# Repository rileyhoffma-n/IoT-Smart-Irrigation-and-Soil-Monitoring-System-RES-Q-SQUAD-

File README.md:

# IoT-Smart-Irrigation-and-Soil-Monitoring-System-RES-Q-SQUAD-
ESE senior design project

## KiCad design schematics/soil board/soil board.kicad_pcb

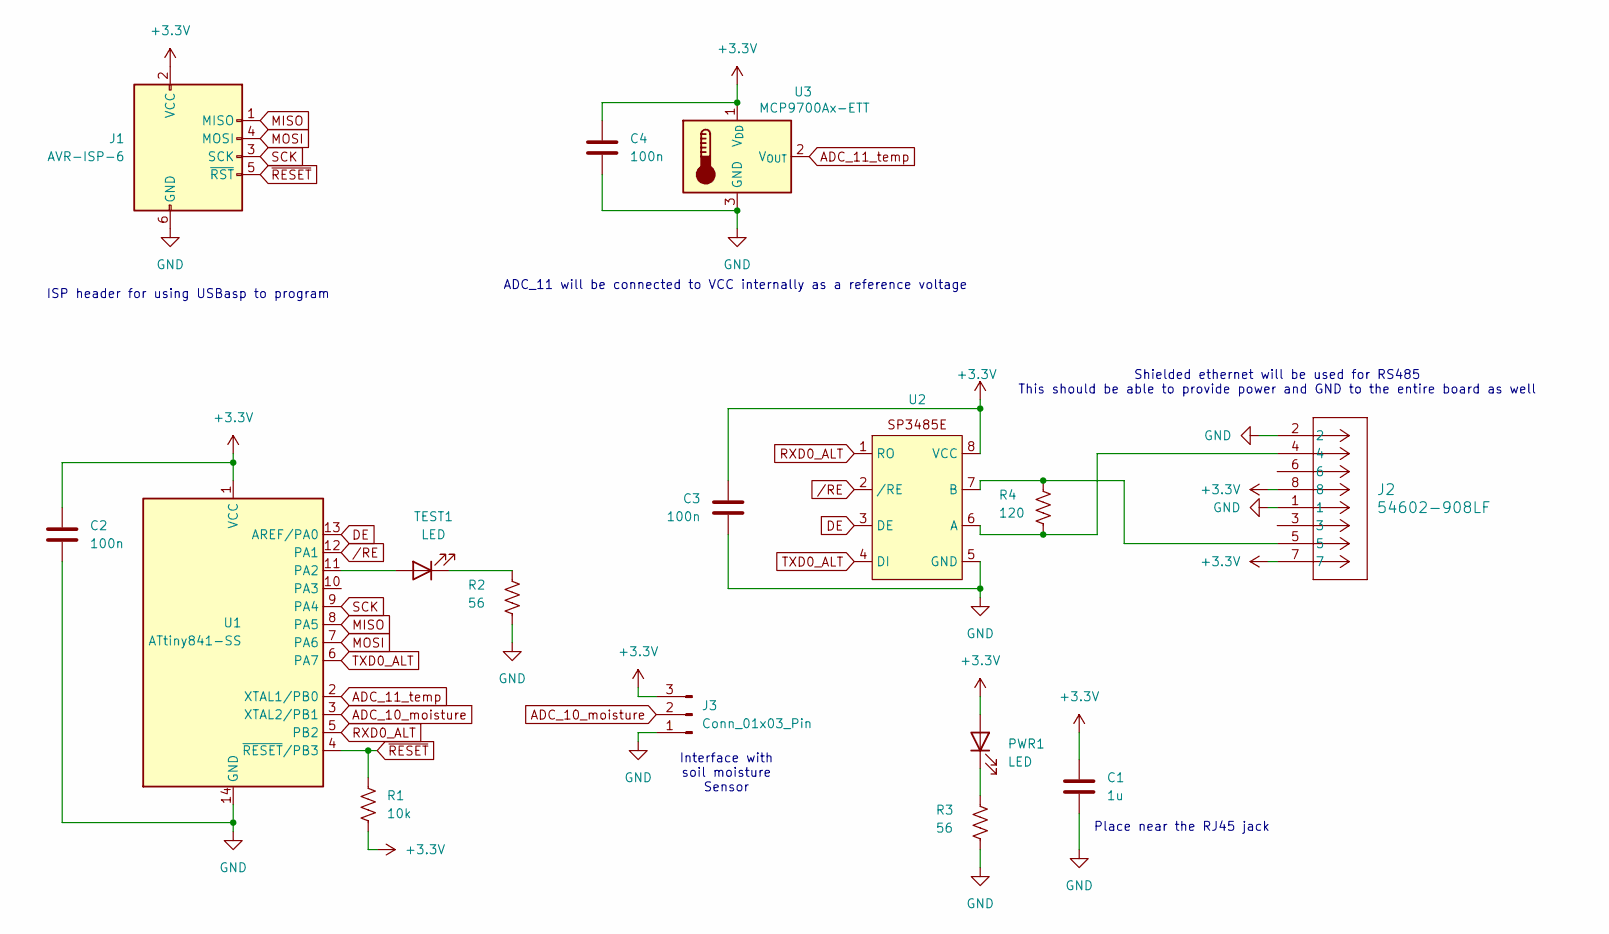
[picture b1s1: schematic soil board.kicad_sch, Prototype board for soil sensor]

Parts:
C1: 1u; R_0805_2012Metric_Pad1.20x1.40mm_HandSolder
C2, C3, C4: 100n; R_0805_2012Metric_Pad1.20x1.40mm_HandSolder
J1: AVR-ISP-6; PinHeader_2x03_P2.54mm_Vertical
J2: 54602-908LF; CONN8_2-908LF_AMP
J3: Conn_01x03_Pin; PinHeader_1x03_P2.54mm_Vertical
PWR1: LED; LED_0805_2012Metric_Pad1.15x1.40mm_HandSolder
R1: 10k; R_0805_2012Metric_Pad1.20x1.40mm_HandSolder
R2, R3: 56; R_0805_2012Metric_Pad1.20x1.40mm_HandSolder
R4: 120; R_0805_2012Metric_Pad1.20x1.40mm_HandSolder
TEST1: LED; LED_0805_2012Metric_Pad1.15x1.40mm_HandSolder
U1: ATtiny841-SS; SOIC-14_3.9x8.7mm_P1.27mm
U2: TSSOP-8_4.4x3mm_P0.65mm
U3: MCP9700Ax-ETT; SOT-23

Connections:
+3.3V: C1.1, C2.1, C3.1, C4.1, J1.2 (VCC), J2.7, J2.8, J3.3, PWR1.2 (A), R1.2, U1.1 (VCC), U2.8 (VCC), U3.1 (V_{DD})
ADC_10_moisture: J3.2, U1.3 (XTAL2/PB1)
ADC_11_temp: U1.2 (XTAL1/PB0), U3.2 (V_{OUT})
DE: U1.13 (AREF/PA0), U2.3 (DE)
GND: C1.2, C2.2, C3.2, C4.2, J1.6 (GND), J2.1, J2.2, J3.1, R2.2, R3.2, U1.14 (GND), U2.5 (GND), U3.3 (GND)
MISO: J1.1 (MISO), U1.8 (PA5)
MOSI: J1.4 (MOSI), U1.7 (PA6)
unnamed: PWR1.1 (K), R3.1
unnamed: TEST1.2 (A), U1.11 (PA2)
unnamed: R2.1, TEST1.1 (K)
unnamed: J2.4, R4.2, U2.6 (A)
unnamed: J2.5, R4.1, U2.7 (B)
RXD0_ALT: U1.5 (PB2), U2.1 (RO)
SCK: J1.3 (SCK), U1.9 (PA4)
TXD0_ALT: U1.6 (PA7), U2.4 (DI)
/RE: U1.12 (PA1), U2.2 (/RE)
~RESET: J1.5 (~RST), R1.1, U1.4 (~RESET/PB3)

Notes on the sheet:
Interface with soil moisture Sensor
Place near the RJ45 jack
ADC_11 will be connected to VCC internally as a reference voltage
Shielded ethernet will be used for RS485 This should be able to provide power and GND to the entire board as well
ISP header for using USBasp to program

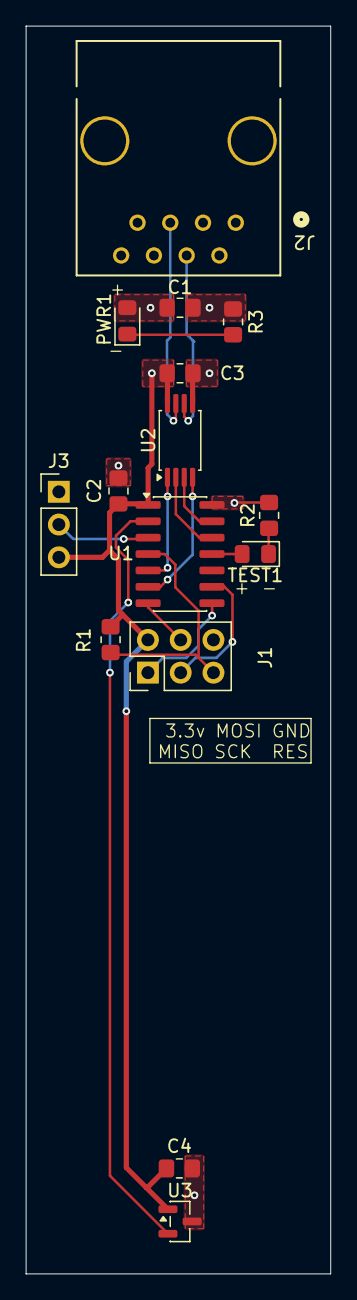
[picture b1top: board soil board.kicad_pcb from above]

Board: 2 copper layers, 23.6 x 96.8 mm, 17 parts (1 on the bottom side), 17 nets.

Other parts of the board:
C_soil1: C; soil_cap

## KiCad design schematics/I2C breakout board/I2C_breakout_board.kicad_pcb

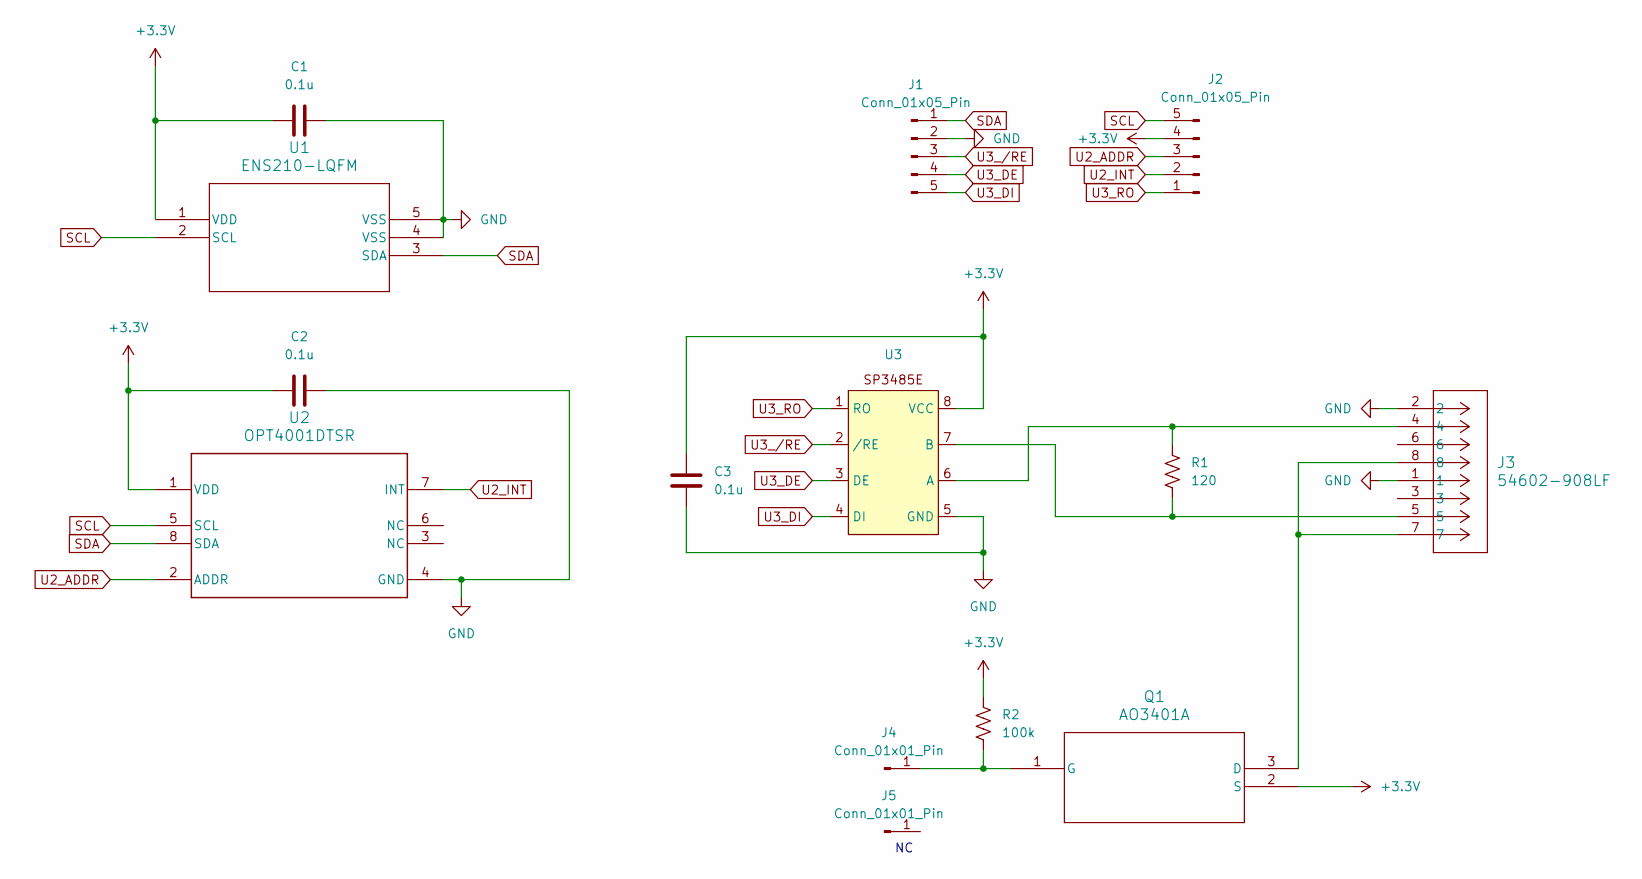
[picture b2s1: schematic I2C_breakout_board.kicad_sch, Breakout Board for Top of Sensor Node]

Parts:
C1, C2, C3: 0.1u; C_0805_2012Metric_Pad1.18x1.45mm_HandSolder
J1, J2: Conn_01x05_Pin; PinHeader_1x05_P2.54mm_Vertical
J3: 54602-908LF; CONN8_2-908LF_AMP
J4, J5: Conn_01x01_Pin; PinHeader_1x01_P2.54mm_Vertical
Q1: AO3401A; SOT-23-3L_AOS-M
R1: 120; R_0805_2012Metric_Pad1.20x1.40mm_HandSolder
R2: 100k; R_0805_2012Metric_Pad1.20x1.40mm_HandSolder
U1: ENS210-LQFM; SON-04-ENS210_2X2_AMS
U2: OPT4001DTSR; DTS0008A-MFG
U3: TSSOP-8_4.4x3mm_P0.65mm

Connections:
+3.3V: C1.1, C2.2, C3.2, J2.4, Q1.2 (S), R2.1, U1.1 (VDD), U2.1 (VDD), U3.8 (VCC)
GND: C1.2, C2.1, C3.1, J1.2, J3.1, J3.2, U1.4 (VSS), U1.5 (VSS), U2.4 (GND), U3.5 (GND)
unnamed: J4.1 (Pin_1_1), Q1.1 (G), R2.2
unnamed: J3.7, J3.8, Q1.3 (D)
unnamed: J3.4, R1.1, U3.6 (A)
unnamed: J3.5, R1.2, U3.7 (B)
SCL: J2.5, U1.2 (SCL), U2.5 (SCL)
SDA: J1.1, U1.3 (SDA), U2.8 (SDA)
U2_ADDR: J2.3, U2.2 (ADDR)
U2_INT: J2.2, U2.7 (INT)
U3_DE: J1.4, U3.3 (DE)
U3_DI: J1.5, U3.4 (DI)
U3_RO: J2.1, U3.1 (RO)
U3_/RE: J1.3, U3.2 (/RE)

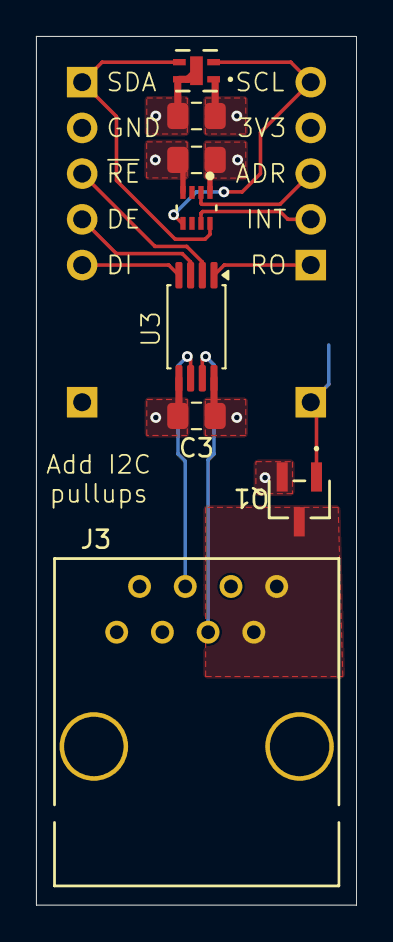
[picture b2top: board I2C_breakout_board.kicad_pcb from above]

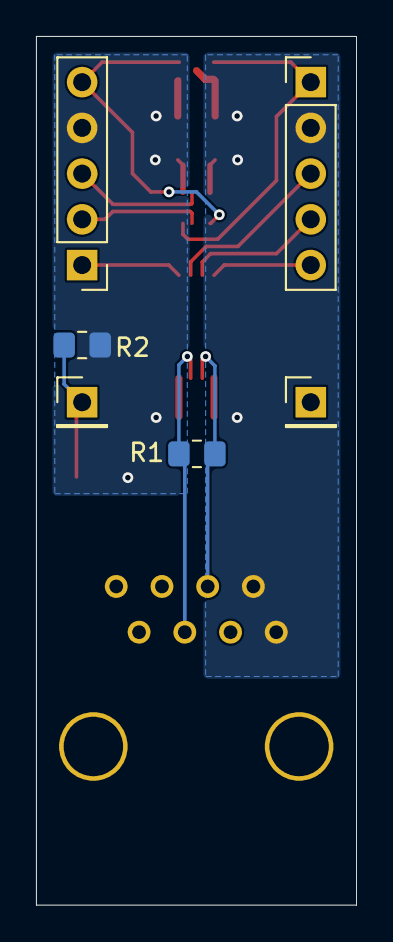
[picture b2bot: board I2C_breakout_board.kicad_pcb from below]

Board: 2 copper layers, 17.8 x 48.3 mm, 14 parts (6 on the bottom side), 14 nets.
